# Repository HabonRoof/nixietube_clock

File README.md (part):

# Nixie Clock Firmware

Open-source ESP-IDF firmware for a multiplexed Nixie clock powered by an ESP32-S3. Hardware display boards include IN-4 and IN-18 variants; at boot the firmware senses `DISPLAY_TYPE` (GPIO 19) and selects an IN-4 (6) or IN-14 (6/8) drive profile. RGB backlighting, audio playback, battery management, and a built-in web configuration UI are included.

Whether you want to hack on display effects, add CLI tools, improve the web UI, or bring up new hardware, this guide will get you building with [PlatformIO](https://platformio.org/) quickly.

## Features

- **Nixie display** — Multiplexed control via PCA9685 PWM drivers and a 74HC238 anode mux (tube count and chip count follow the detected display-board profile).
- **RGB backlight** — WS2812 addressable LEDs (4 per tube) with static, breath, rainbow, and off effects.
- **Audio** — DFPlayer Mini integration for sound effects and announcements.
- **RTC** — DS3231 for precise timekeeping with periodic resync to ESP32 system time.
- **Web UI** — On-demand config Wi-Fi AP (`NixieClock-XXXX` / `nixie2026`) with HTTP settings; long-press **button 1 + button 2** (3 s) to enter config mode.
- **NTP sync** — Optional home WiFi credentials; daily ~06:00 local brief STA session writes NTP to DS3231 and verifies RTC error < 1 min (retries on failure).
- **Buttons** — Debounced physical inputs for display mode, backlight profile, and interactive modes.
- **Hibernate mode** — Scheduled daily window turns off tubes and LED backlight. Press any button for a 5-second clock preview (tubes at fixed brightness 50, LED off).
- **Idle standby** — After 1 minute without button presses in clock mode, dim nixie and backlight brightness to 25% of the active profile; any button press restores full brightness.
- **Auto cathode anti-poisoning** — Every 15 minutes, run the same cathode-poisoning digit sweep as manual mode, then auto-return to the clock.
- **Serial CLI** — Interactive console for development, diagnostics, and power-rail control.
- **Power management** — BQ25601 battery charger, BQ27441 fuel gauge, and switched HV / DFPlayer rails.
- **Persistent settings** — Clock preferences stored in NVS and restored on boot.
- **Modular architecture** — FreeRTOS daemons coordinated by a central system controller.

## Developing with PlatformIO

This project uses **PlatformIO + ESP-IDF**. You can work from VS Code / Cursor or from the CLI.

### 1. Install tools

1. Install [Git](https://git-scm.com/) and [Python 3](https://www.python.org/downloads/) (needed for the git-version build script).
2. Install either:
   - **Recommended:** [VS Code](https://code.visualstudio.com/) or Cursor with the [PlatformIO IDE](https://platformio.org/install/ide?install=vscode) extension, or
   - [PlatformIO Core (CLI)](https://docs.platformio.org/en/latest/core/installation.html) alone.
   For now, the PlatformIO for cursor is not stable, so I recommand to use VSCode to compile and use Cursor for coding. 

Opening this repo in VS Code / Cursor should prompt you to install the recommended `platformio.platformio-ide` extension (see `.vscode/extensions.json`).

### 2. Clone and open the project

```bash
git clone https://github.com/HabonRoof/nixietube_clock.git
cd nixietube_clock
```

In VS Code / Cursor: **File → Open Folder** and select the repo root (the folder that contains `platformio.ini`).

First build will download the Espressif platform, ESP-IDF toolchain, and dependencies into `.pio/` — expect a few minutes on a clean machine.

### 3. Pick a build environment

Defined in `platformio.ini`:

| Environment | Board | Use case |
| :--- | :--- | :--- |
| `esp32_s3_devkitc_1` | ESP32-S3-DevKitC-1 | General development / bring-up |
| `esp32_s3_nixie` (default) | Custom `esp32-s3-nixie` (`boards/`) | Production Nixie clock board |

Switch the active env in the PlatformIO status bar, or pass `-e <name>` on the CLI.

### 4. Everyday commands

| Action | CLI | VS Code / Cursor (PlatformIO) |
| :--- | :--- | :--- |
| Build | `pio run` | Build (✓) |
| Flash | `pio run -t upload` | Upload (→) |
| Serial monitor | `pio run -t monitor` | Serial Monitor (🔌) |
| Build + flash + monitor | `pio run -t upload && pio run -t monitor` | Upload and Monitor |
| Clean | `pio run -t clean` | Clean |
| Build for Nixie board | `pio run -e esp32_s3_nixie` | Select `esp32_s3_nixie` env, then Build |

Serial monitor is **115200 baud** (8N1). After connect you should see boot logs and the CLI prompt `nixie_clock> `.

Useful PlatformIO tips:

```bash
# Rebuild from a clean slate
pio run -t clean && pio run

# Flash a specific env, then open the monitor
pio run -e esp32_s3_devkitc_1 -t upload
pio run -t monitor

# List detected serial ports if upload fails
pio device list
```

The build embeds the current git commit hash via `generate_git_version.py` (`get_fw_version` in the CLI).

### 5. Verify you are up and running

1. Flash firmware and open the serial monitor.
2. Type `help` at `nixie_clock> ` to list CLI commands.
3. **Long-press button 1 + button 2** (3 s together) to open the config Wi-Fi AP. Nixie tubes show a 4-digit session code; join `NixieClock-XXXX` (password `nixie2026`) and open `http://192.168.8.8/`.

If something fails to compile or upload, check:

- Use USB Type-A to Type-C cable, the hardware is not support to connect C to C cable for uploading.
- The board is in download mode / USB cable is data-capable.
- The correct env is selected (`esp32_s3_devkitc_1` vs `esp32_s3_nixie`).
- Python can run `generate_git_version.py` from the project root.
- Antivirus or missing udev/driver issues are not blocking the serial port (Windows often needs the CP2102 USB serial driver).

### 6. Where to start hacking

| Goal | Start here |
| :--- | :--- |
| Boot / wiring of subsystems | `src/main.cpp` |
| Mode logic, time, settings | `src/system_controller.*` |
| Tubes / LED effects | `src/daemons/display_daemon.*` |
| Buttons | `src/daemons/input_daemon.*` |
| Audio / DFPlayer | `src/daemons/audio_daemon.*` |
| Serial commands | `src/daemons/cli_daemon.*` |
| Web settings UI | `src/web_server.cpp`, `src/web_page.cpp` |
| Device drivers | `lib/drivers/`, `lib/include/` |
| Shared messages / state | `lib/include/message_types.h`, `src/system_state.*` |

## Software Structure

The firmware is split into clear layers so new contributors can find the right file quickly.

```text
┌─────────────────────────────────────────────────────────────┐
│  Interfaces                                                 │
│    WebServer  ·  CliDaemon  ·  InputDaemon (buttons)        │
├─────────────────────────────────────────────────────────────┤
│  Coordination                                               │
│    SystemController  ·  SystemState (NVS)                   │
├─────────────────────────────────────────────────────────────┤
│  FreeRTOS daemons                                           │
│    DisplayDaemon  ·  AudioDaemon                            │
├─────────────────────────────────────────────────────────────┤
│  App drivers / services                                     │
│    NixieDriver · LedDriver · AudioDriver                    │
│    PowerController · ChargerController · GasgaugeService    │
├─────────────────────────────────────────────────────────────┤
│  Hardware drivers (lib/drivers)                             │
│    PCA9685 · WS2812 · DFPlayer · DS3231 · BQ25601 · BQ27441 │
└─────────────────────────────────────────────────────────────┘
```

### Directory map

```text
nixietube_clock/
├── platformio.ini          # PlatformIO envs, ESP-IDF, build flags
├── boards/                 # Custom board JSON (esp32-s3-nixie)
├── generate_git_version.py # Embeds git hash into the firmware
│
├── src/                    # Application code (what most PRs touch)
│   ├── main.cpp            # Boot: NVS, drivers, start daemons
│   ├── system_controller.* # Central coordinator (time, modes, settings)
│   ├── system_state.*      # Thread-safe settings / battery / time + NVS
│   ├── web_server.*        # Wi-Fi AP + HTTP API
│   ├── web_page.*          # Embedded settings HTML/JS
│   ├── settings_json.*     # ClockSettings ↔ nested JSON
│   ├── web_json.*          # HTTP JSON body / response helpers
│   ├── nixie_driver.*      # High-level tube multiplexing
│   ├── led_driver.*        # High-level WS2812 control
│   ├── audio_driver.*      # High-level DFPlayer wrapper
│   ├── power_controller.*  # HV / DFPlayer rail switching
│   ├── charger_controller.*
│   ├── gasgauge_service.*
│   ├── color_model.cpp     # Color helpers for backlight
│   └── daemons/
│       ├── display_daemon.*  # Nixie + LED effects @ 50 Hz
│       ├── audio_daemon.*    # Async audio commands
│       ├── input_daemon.*    # Button debounce → SystemController
│       └── cli_daemon.*      # Serial console
│
├── lib/
│   ├── include/            # Public headers / interfaces / message types
│   └── drivers/            # Low-level IC drivers (I2C/UART/RMT/GPIO)
│       ├── pca9685/
│       ├── ws2812/
│       ├── dfplayer/
│       ├── ds3231/
│       ├── bq25601/
│       ├── bq27441/
│       ├── i2c_bus/
│       ├── power_switch/
│       └── display_board/
│
├── hardware/               # KiCad schematics & PCBs (main, display, HV)
├── test/                   # Manual CLI tests and component experiments
└── doc/                    # Datasheets, photos, architecture drawings
    ├── web_api.md          # HTTP JSON API schemas
    ├── state_machine.drawio  # Behavioral modes (six pages, kept in sync with firmware)
    └── structure.drawio    # Early aspirational block diagram (outdated)
```

### Responsibility cheat sheet

| Module | Role |
| :--- | :--- |
| `main.cpp` | Creates drivers/services, wires dependencies, starts tasks |
| `SystemController` | Owns RTC sync, display mode / backlight / alarm logic; single writer for settings |
| `SystemState` | Shared snapshots + NVS load/save |
| `DisplayDaemon` | Tube digits, LED effects, 50 Hz update loop |
| `AudioDaemon` | Plays/pauses tracks; powers DFPlayer rail via `PowerController` |
| `InputDaemon` | Polls/debounces BTN_0–2 and posts presses to `SystemController` |
| `CliDaemon` / `WebServer` | External control surfaces; request settings through `SystemController` |
| `lib/drivers/*` | Talk to chips; keep bus/register details out of app logic |

Cross-task communication uses FreeRTOS queues and types in `lib/include/message_types.h`. Prefer posting messages (or `SystemController::request_settings_update()`) over reaching into another daemon’s private state.

## Hardware Configuration

Pin assignments are defined in `src/system_controller.cpp` and `lib/drivers/power_switch/gpio_power_switch.h`.

| Peripheral | Pin Name | GPIO | Description |
| :--- | :--- | :--- | :--- |
| **I2C0** | SDA | GPIO 6 | PCA9685 (display), BQ25601, BQ27441 |
| | SCL | GPIO 5 | I2C0 clock (400 kHz) |
| **I2C1** | SDA | GPIO 18 | DS3231 RTC, LTR-303 (display) |
| | SCL | GPIO 17 | I2C1 clock (400 kHz) |
| **UART** | TX | GPIO 42 | Audio TX → DFPlayer RX |
| | RX | GPIO 41 | Audio RX ← DFPlayer TX |
| **GPIO** | RTC_INT | GPIO 2 | DS3231 interrupt (active low) |
| | BTN_0 | GPIO 8 | Alarm stop / pomodoro start / divergence re-trigger |
| | BTN_1 | GPIO 12 | Display mode cycle |
| | BTN_2 | GPIO 13 | Backlight profile cycle |
| | PCA_OE | GPIO 4 | PCA9685 output enable (active low) |
| | ANODE_A0–A2 | GPIO 9–11 | 74HC238 anode mux address lines |
| | DISPLAY_TYPE | GPIO 19 | Analog strap for display-board type (ADC2 CH8) |
| | HV_PWR | GPIO 15 | HV power rail enable (via `GpioPowerSwitch`) |
| | DF_PWR | GPIO 16 | DFPlayer power rail enable (via `GpioPowerSwitch`) |
| **RMT** | LED_DATA | GPIO 7 | WS2812 LED data line |

`DISPLAY_TYPE` strap voltages map to firmware profiles: ~0 V → IN-4 (6 tubes, 4× PCA9685); ~1.65 V → IN-14 (8 tubes, 5× PCA9685); ~3.3 V → IN-14 (6 tubes, 4× PCA9685). KiCad projects under `hardware/` include `display_board_in4` and `display_board_in18` (IN-18 boards use the matching strap / profile configured on the PCB).

## Architecture

The firmware runs on FreeRTOS and uses a daemon-based design. `SystemState` holds shared, thread-safe snapshots of settings, battery, and time status.

```mermaid
flowchart TB
    subgraph Interfaces
        Web[WebServer]
        CLI[CliDaemon]
        IN[InputDaemon]
    end

    SC[SystemController]
    DD[DisplayDaemon]
    AD[AudioDaemon]
    CC[ChargerController]
    PC[PowerController]

    Web --> SC
    CLI --> SC
    CLI --> CC
    CLI --> PC
    CLI --> AD
    IN --> SC

    SC --> DD
    SC --> AD
    SC --> SystemState[(SystemState / NVS)]

    DD --> Nixie[NixieDriver / PCA9685]
    DD --> LED[LedDriver / WS2812]
    AD --> Audio[AudioDriver / DFPlayer]
    AD --> PC
    SC --> RTC[DS3231]
    SC --> GG[GasgaugeService / BQ27441]
    CC --> Charger[BQ25601]
    PC --> Rails[HV & DFPlayer rails]
```

### System Controller (`src/system_controller.cpp`)

Central coordinator that:

- Initializes I2C, UART, RMT, and GPIO peripherals.
- Owns the DS3231 RTC and maintains ESP32 system time (UTC).
- Periodically resyncs from the RTC and publishes time status.
- Polls the BQ27441 fuel gauge and updates battery status.
- Dispatches 1 Hz time updates to `DisplayDaemon`.
- Handles button presses from `InputDaemon` (modes, backlight, pomodoro / alarm).
- Accepts thread-safe settings changes from the web UI and CLI.

### Display Daemon (`src/daemons/display_daemon.cpp`)

Manages all visual output:

- Drives Nixie tubes via `NixieDriver` (dedicated high-priority multiplexing task).
- Drives LED backlights via `LedDriver`.
- Runs the LED effects engine (static, breath, rainbow, off).
- Updates hardware at 50 Hz.

#### Display modes (BTN_1 cycle)

Press **BTN_1** to cycle through display modes in this order:

1. **Clock** (`HHMMSS`) — normal time display
2. **Date** (`YYMMDD`) — current date
3. **Pomodoro** — 25-minute work / 5-minute break timer
4. **Divergence meter** — random digit animation (auto-returns to clock)
5. **Cathode poisoning** — digit sweep on all tubes (auto-returns to clock)

**Pomodoro mode:** On entry the display shows `002500` with a static red backlight (brightness follows your profile). Press **BTN_0** to start the countdown; the backlight breathes red during work and green during break. Work and break sessions alternate automatically until you cycle away with **BTN_1**, which restores your backlight profile.

### Input Daemon (`src/daemons/input_daemon.cpp`)

Polls the three front-panel buttons every 20 ms with debounce / inter-press filtering, then posts press events to `SystemController`. **Button 2** short press cycles backlight profiles; **long press button 1 + button 2** (3 s) opens or closes the config Wi-Fi AP. Pin map: `lib/include/button_config.h`.

### Audio Daemon (`src/daemons/audio_daemon.cpp`)

Handles asynchronous audio commands (play, stop, volume) and communicates with the DFPlayer Mini. Uses `PowerController` to switch the DFPlayer power rail.

### Web Server (`src/web_server.cpp`, `src/web_page.cpp`)

On-demand config Wi-Fi AP and embedded HTTP server (active only in config mode):

| Setting | Value |
| :--- | :--- |
| Enter config | Long-press button 1 + button 2 for 3 s (same combo exits when AP is active) |
| SSID | `NixieClock-XXXX` (random 4-digit code each session; shown on Nixie tubes) |
| Password | `nixie2026` |
| AP IP | `192.168.8.8` |
| Timeout | 15 min max, or 2 min after all clients disconnect |

Connect to the AP and open `http://192.168.8.8/`. Use **完成並關閉設定 WiFi** when done.

| Endpoint | Method | Description |
| :--- | :--- | :--- |
| `/` | GET | Settings web UI |
| `/api/settings` | GET/POST | Clock settings (JSON); see [doc/web_api.md](doc/web_api.md) |
| `/api/ap/status` | GET | Config AP SSID, session code, remaining time |
| `/api/ap/stop` | POST | Stop config AP (deauth + shutdown) |
| `/api/wifi` | GET/POST/DELETE | Home WiFi for daily NTP sync |
| `/api/ntp/status` | GET | Last NTP sync status |
| `/api/time` | GET | Local time, RTC status, temperature |
| `/api/audio/*` | GET/POST | MP3 tracks and playback |

Home WiFi credentials enable a brief daily STA session at **06:00 local** for NTP → DS3231 sync (always write, verify RTC within 1 min, retry up to 3×); WiFi is off the rest of the time.

Full schemas: [doc/web_api.md](doc/web_api.md). Without hardware, `python3 scripts/mock_web_ui.py` serves this same page at `http://127.0.0.1:8080/` with in-memory stand-ins for the JSON API. See [scripts/README.md](scripts/README.md).

Configurable settings include timezone offset, alarm, backlight, nixie brightness/transition, volume, profiles, hibernation, and home WiFi. The web **Light** tab provides live display preview; **Save 1–4** commits a profile. Short-press button 2 to switch profiles on the device.

### CLI Daemon (`src/daemons/cli_daemon.cpp`)

Interactive serial console for development, diagnostics, and factory setup. Connect at **115200 baud** (8N1, no flow control) via USB or UART. The prompt is `nixie_clock> `. Type `help` for a summary of all commands.

```bash
pio run -t monitor
```

#### Display and backlight

| Command | Description |
| :--- | :--- |
| `set_nixie --number <n>` | Display a 6-digit number on the tubes |
| `set_backlight --rgb R,G,B --brightness N` | Set backlight color and brightness (0–255) |

#### Device info

| Command | Description |
| :--- | :--- |
| `get_uuid` | Wi-Fi MAC-based device ID |
| `get_hw_version` | ESP32-S3 chip and board revision |
| `get_fw_version` | Git commit hash and ESP-IDF version |
| `reboot` | Restart the device |

#### RTC and alarm (`rtctool`)

The DS3231 RTC stores **UTC** internally; CLI time and alarm values are **local wall clock** and are converted using the configured timezone offset. Set operations are asynchronous — run `rtctool read` afterward to confirm.

| Subcommand | Description |
| :--- | :--- |
| `rtctool read` | Read local time, UTC epoch, timezone, calibration/OSF status, temperature, and alarm settings |
| `rtctool set_tz <offset_hours>` | Set timezone offset (-12..+14) |
| `rtctool set_time <YYYY-MM-DD HH:MM:SS>` | Calibrate RTC and system clock (marks RTC as calibrated) |
| `rtctool set_alarm <HH:MM:SS> [--enable\|--disable] [--track <n>]` | Set daily alarm time; enables alarm by default |

Example workflow:

```text
nixie_clock> rtctool set_tz 8
nixie_clock> rtctool set_time 2026-07-06 16:30:00
nixie_clock> rtctool set_alarm 07:30:00 --enable --track 1
nixie_clock> rtctool read
```

To disable the alarm without changing its time:

```text
nixie_clock> rtctool set_alarm 07:30:00 --disable
```

#### Power and charging

| Command | Description |
| :--- | :--- |
| `get_bq25601_status` | Read BQ25601 charger status registers |
| `enable_charging` / `disable_charging` | Control battery charging |
| `enable_hv` / `disable_hv` | Control HV power rail |
| `enable_df_power` / `disable_df_power` | Control DFPlayer power rail |

#### DFPlayer audio (`dftool`)

Commands talk to the `AudioDaemon`, which powers the DFPlayer rail automatically when needed. Place MP3 files in an `mp3` folder on the SD card root and name them `0001.mp3`, `0002.mp3`, etc. (up to 9999). Track numbers match the numeric prefix in each filename.

| Subcommand | Description |
| :--- | :--- |
| `dftool list` | List tracks in the SD card `mp3/` folder |
| `dftool status` | Show current track, playback state, and track count |
| `dftool play <track> [--loop]` | Play a track; add `--loop` for repeat |
| `dftool toggle <track>` | Play/pause toggle (same behavior as the web UI) |
| `dftool pause` | Pause playback |
| `dftool resume` | Resume playback |
| `dftool stop` | Stop playback |
| `dftool next` | Play next track |
| `dftool prev` | Play previous track |
| `dftool volume <0-30>` | Set volume (DFPlayer range) |
| `dftool vol_up` / `dftool vol_down` | Step volume up or down |

Example workflow:

```text
nixie_clock> dftool list
nixie_clock> dftool play 1
nixie_clock> dftool status
nixie_clock> dftool pause
nixie_clock> dftool resume
nixie_clock> dftool volume 20
nixie_clock> dftool stop
```

#### Fuel gauge (`ggtool`)

| Subcommand | Description |
| :--- | :--- |
| `ggtool status` | Probe BQ27441 device info and gauging readiness |
| `ggtool read` | Read live SOC, SOH, voltage, and current |
| `ggtool cache` | Read last cached battery values from `SystemState` |
| `ggtool peek <reg_hex> [len]` | Dump raw register bytes |
| `ggtool block [class] [index]` | Dump a 32-byte state block |
| `ggtool config [mAh]` | Configure design capacity |

See `test/test_cli/README.md` for a manual test plan and automated test script.

### Drivers (`lib/drivers/`, `src/*_driver.cpp`)

| Driver | Role |
| :--- | :--- |
| `NixieDriver` | PCA9685 multiplexing; chip/tube count from `display_board_config` profile |
| `LedDriver` | RMT-based WS2812 control |
| `AudioDriver` | High-level DFPlayer Mini interface |
| `Ds3231` | RTC read/write and temperature |
| `Bq25601` | Battery charger IC |
| `Bq27441` | Fuel gauge IC |
| `GpioPowerSwitch` | HV and DFPlayer power-rail switching |

## Development Guide

### Adding a New LED Effect

1. Add a method such as `run_my_effect(uint32_t dt_ms)` in `DisplayDaemon`.
   Use `apply_backlight_to_all(state)` or manipulate `led_driver_` directly.
2. Add an entry to the `LedEffectType` enum in `display_daemon.h`.
3. Update `DisplayDaemon::process_message` to handle the new effect type.
4. Update `DisplayDaemon::update_effects` to call the new method.
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
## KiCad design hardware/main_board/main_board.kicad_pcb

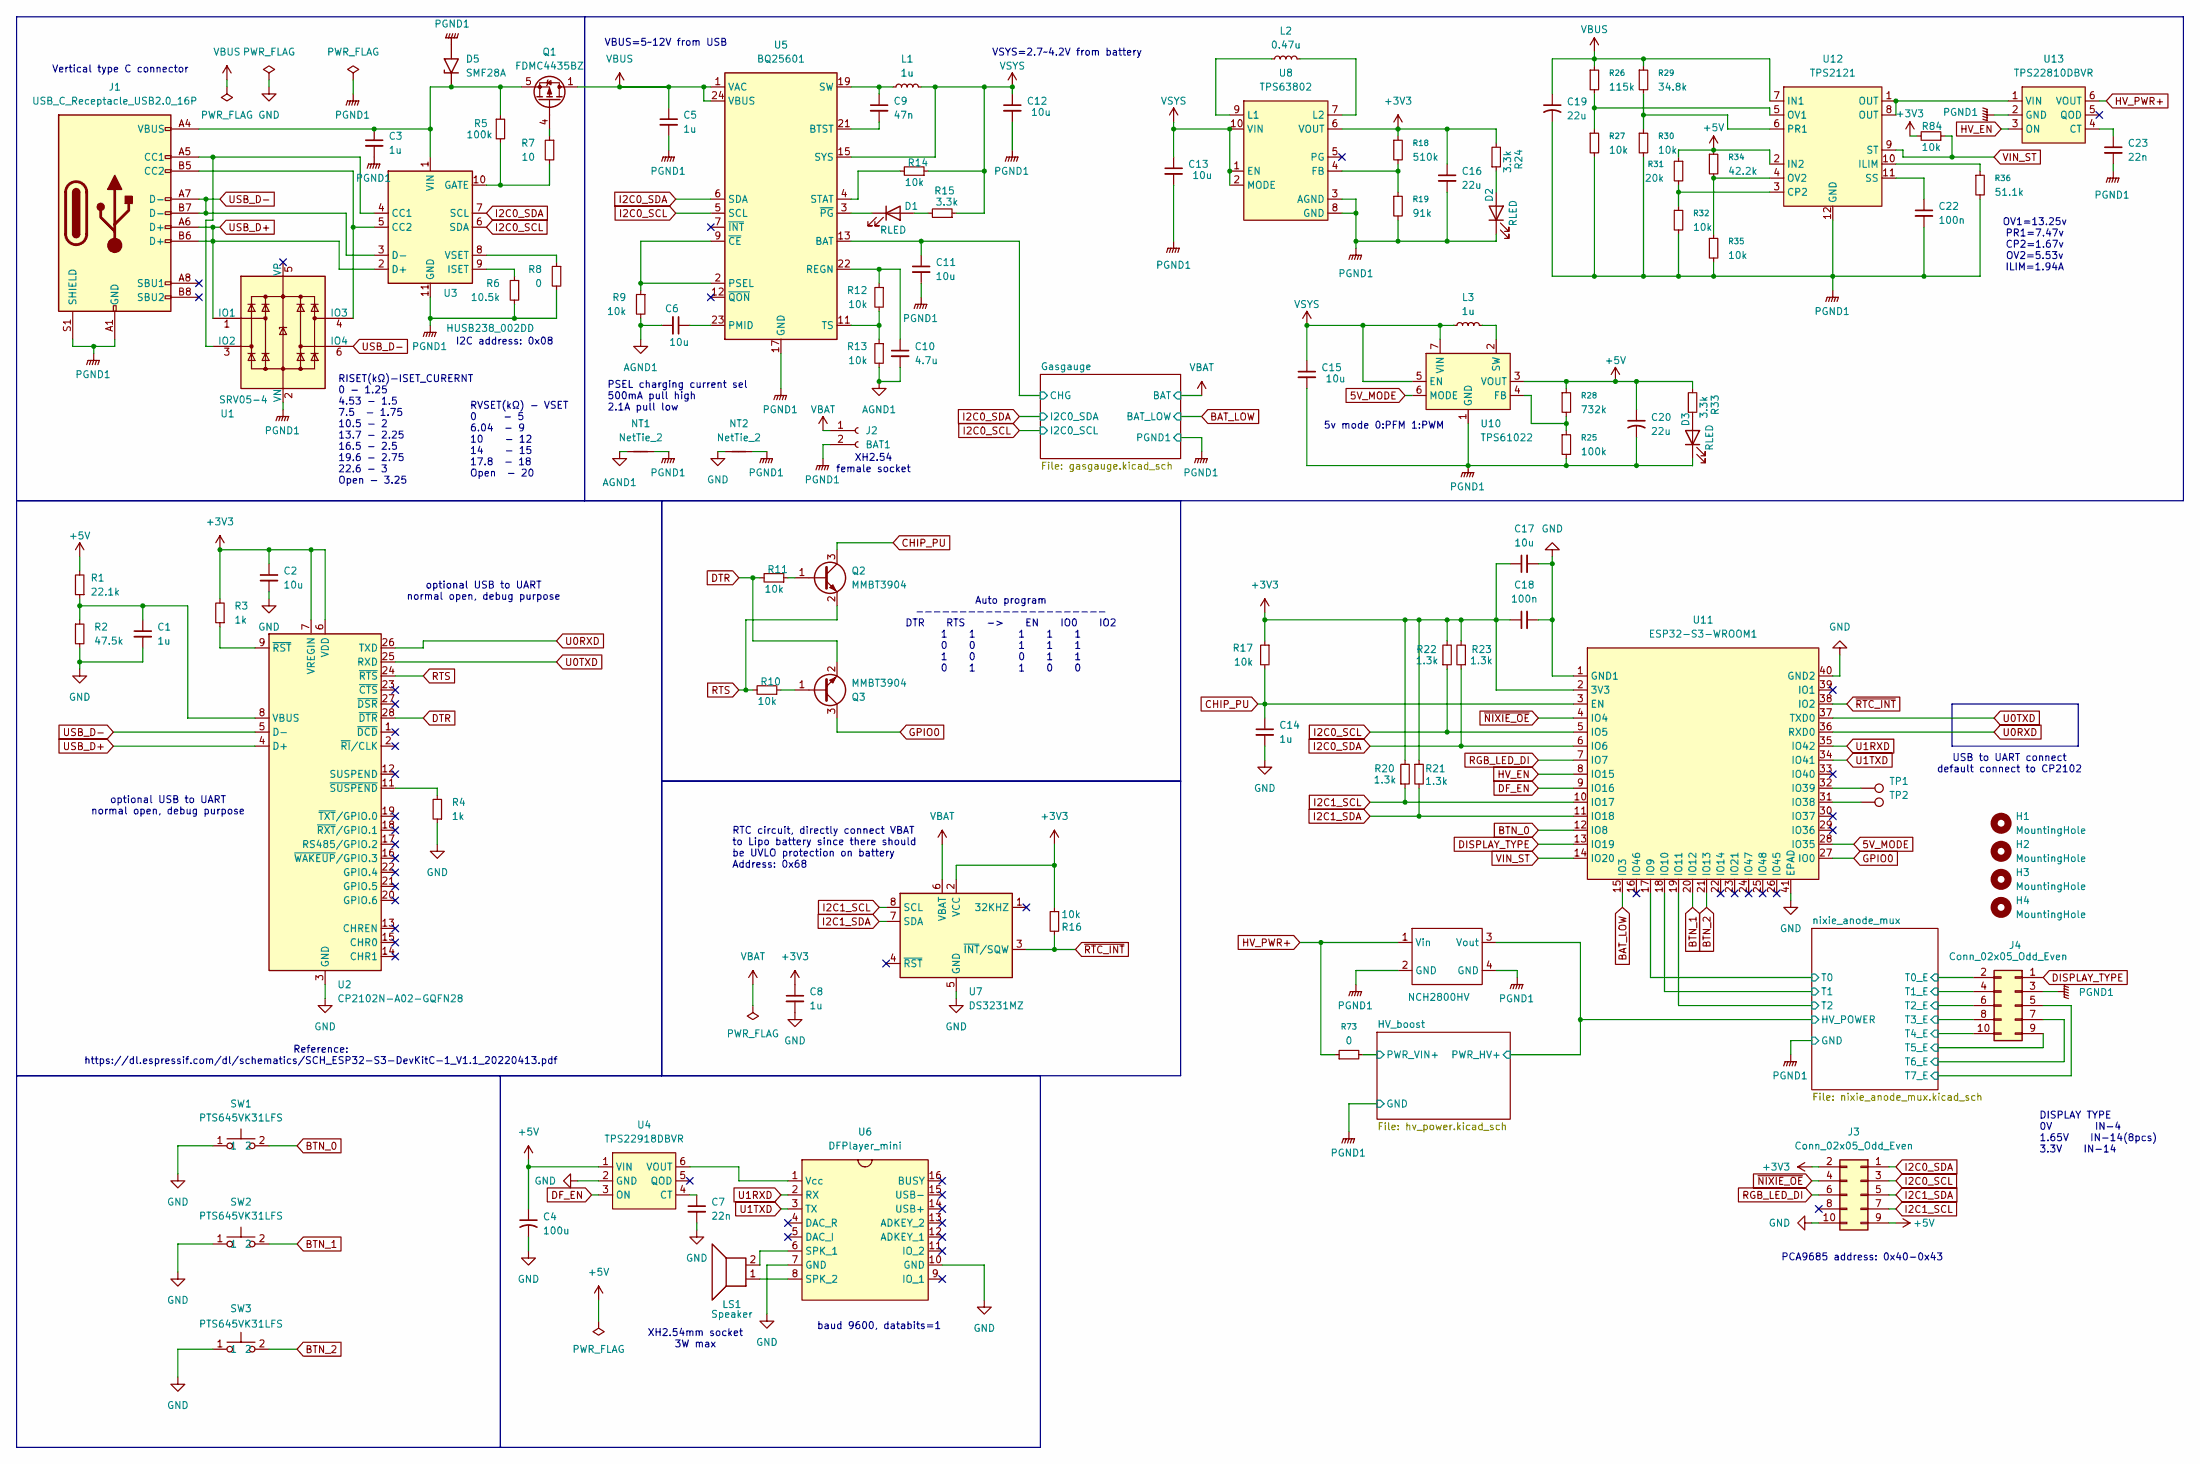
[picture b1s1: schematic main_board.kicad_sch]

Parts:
C1, C3, C5, C8, C14: 1u; C_0603_1608Metric; LCSC PN C5199872
C2, C6, C11, C17: 10u; C_0603_1608Metric; LCSC PN C19702
C4: 100u; C_Elec_6.3x5.4; LCSC PN C2887276
C7: 22n; C_0603_1608Metric; LCSC PN C106222
C9: 47n; C_0603_1608Metric; LCSC PN C1622
C10: 4.7u; C_0603_1608Metric; LCSC PN C18185770
C12: 10u; C_0805_2012Metric; LCSC PN C6119932
C13, C15: 10u; CP_EIA-2012-12_Kemet-R; LCSC PN C129234
C16: 22u; C_0805_2012Metric; LCSC PN C23692981
C18, C22: 100n; C_0402_1005Metric; LCSC PN C1525
C19, C20: 22u; C_Elec_5x5.4; LCSC PN C970662
C23: 22n; C_0402_1005Metric; LCSC PN C1532
D1, D2, D3: RLED; LED_0603_1608Metric; LCSC PN C2286
D5: SMF28A; D_SMF
H1, H2, H3, H4: MountingHole; MountingHole_3.2mm_M3_DIN965
J1: USB_C_Receptacle_USB2.0_16P; USB_C_Receptacle_G-Switch_GT-USB-7051x; LCSC PN C2843970
J2: BAT1; JST_PH_S2B-PH-SM4-TB_1x02-1MP_P2.00mm_Horizontal; LCSC PN C3029440
J3, J4: Conn_02x05_Odd_Even; PinHeader_2x05_P2.00mm_Vertical; LCSC PN C42385473
L1: 1u; L_Wuerth_PMCI-252010; LCSC PN C696436
L2: 0.47u; Murata_201612E; LCSC PN C668312
L3: 1u; L_Coilcraft_XAL6030-XXX; LCSC PN C5157561
LS1: Speaker; JST_PH_S2B-PH-SM4-TB_1x02-1MP_P2.00mm_Horizontal; LCSC PN C3029440
NT1, NT2: NetTie_2; NetTie-2_SMD_Pad0.5mm
Q1: FDMC4435BZ; VSON-8_3.3x3.3mm_P0.65mm_NexFET; LCSC PN C556450
Q2, Q3: MMBT3904; SOT-23; LCSC PN C81464
R1: 22.1k; R_0402_1005Metric; LCSC PN C43473
R2: 47.5k; R_0402_1005Metric; LCSC PN C103064
R3, R4: 1k; R_0402_1005Metric; LCSC PN C11702
R5, R25: 100k; R_0402_1005Metric; LCSC PN C25741
R6: 10.5k; R_0402_1005Metric; LCSC PN C25850
R7: 10; R_0402_1005Metric; LCSC PN C25077
R8: 0; R_0402_1005Metric; LCSC PN C17168
R9, R10, R11, R12, R13, R14, R16, R17, R84: 10k; R_0402_1005Metric; LCSC PN C25744
R15, R24, R33: 3.3k; R_0402_1005Metric; LCSC PN C25890
R18: 510k; R_0402_1005Metric; LCSC PN C100463
R19: 91k; R_0402_1005Metric; LCSC PN C284722
R20, R21: 1.3k; R_0402_1005Metric; LCSC PN C25900
R22, R23: 1.3k; R_0402_1005Metric; LCSC PN C881388
R26: 115k; R_0603_1608Metric; LCSC PN C227555
R27, R30, R32, R35: 10k; R_0603_1608Metric; LCSC PN C98220
R28: 732k; R_0402_1005Metric; LCSC PN C27016
R29: 34.8k; R_0603_1608Metric; LCSC PN C23141
R31: 20k; R_0603_1608Metric; LCSC PN C4184
R34: 42.2k; R_0603_1608Metric; LCSC PN C227896
R36: 51.1k; C_0603_1608Metric; LCSC PN C23072
R73: 0; R_0603_1608Metric; LCSC PN C21189
SW1, SW2, SW3: PTS645VK31LFS; LCSC PN C2804591
TP1, TP2: TestPoint; TestPoint_Pad_1.5x1.5mm
U1: SRV05-4; SOT-23-6; LCSC PN C13612
U2: CP2102N-A02-GQFN28; QFN-28-1EP_5x5mm_P0.5mm_EP3.35x3.35mm; LCSC PN C964632
U3: HUSB238_002DD; WDFN-10-1EP_3x3mm_P0.5mm_EP1.8x2.5mm; LCSC PN C7471904
U4: TPS22918DBVR; SOT-23-6; LCSC PN C131941
U5: BQ25601; Texas_RTW_WQFN-24-1EP_4x4mm_P0.5mm_EP2.7x2.7mm_ThermalVias; LCSC PN C468236
U6: DFPlayer_mini
U7: DS3231MZ; SOIC-8_3.9x4.9mm_P1.27mm; LCSC PN C107410
U8: TPS63802; VSON-10-HR-DLA; LCSC PN C2845237
U9: NCH2800HV; NCH8200HV
U10: TPS61022; Texas_RWU0007A_VQFN-7_2x2mm_P0.5mm; LCSC PN C2071784
U11: ESP32-S3-WROOM1; ESP32-S3-WROOM-1; LCSC PN C2913198
U12: TPS2121; Texas_VQFN-HR-12_2x2.5mm_P0.5mm_ThermalVias; LCSC PN C2156025
U13: TPS22810DBVR; SOT-23-6; LCSC PN C205990

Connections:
5V_MODE: U10.6 (MODE), U11.28 (IO35)
+3V3: C2.1, C8.1, C16.1, C17.1, C18.1, J3.2, R3.2, R16.1, R17.1, R18.1, R20.2, R21.1, R22.2, R23.2, R24.2, R84.2, U2.6 (VDD), U2.7 (VREGIN), U7.2 (VCC), U8.6 (VOUT), U11.2 (3V3); also elsewhere on the board
+5V: C4.1, C20.1, J3.9, R1.2, R28.1, R31.1, R33.2, R34.1, U4.1 (VIN), U10.3 (VOUT), U12.2 (IN2)
/Gasgauge/CHG: C11.1, U5.13 (BAT), U5.14 (BAT); also elsewhere on the board
/HV_boost/PWR_HV+: U9.3 (Vout); also elsewhere on the board
/HV_boost/PWR_VIN+: R73.2; also elsewhere on the board
/nixie_anode_mux/T0: U11.17 (IO9); also elsewhere on the board
/nixie_anode_mux/T0_E: J4.2; also elsewhere on the board
/nixie_anode_mux/T1: U11.18 (IO10); also elsewhere on the board
/nixie_anode_mux/T1_E: J4.4; also elsewhere on the board
/nixie_anode_mux/T2: U11.19 (IO11); also elsewhere on the board
/nixie_anode_mux/T2_E: J4.6; also elsewhere on the board
/nixie_anode_mux/T3_E: J4.8; also elsewhere on the board
/nixie_anode_mux/T4_E: J4.10; also elsewhere on the board
/nixie_anode_mux/T5_E: J4.9; also elsewhere on the board
/nixie_anode_mux/T6_E: J4.7; also elsewhere on the board
/nixie_anode_mux/T7_E: J4.5; also elsewhere on the board
AGND1: C6.2, C10.2, NT1.1, R9.2, R13.2
BAT_LOW: U11.15 (IO3); also elsewhere on the board
BTN_0: SW1.2, U11.12 (IO8)
BTN_1: SW2.2, U11.20 (IO12)
BTN_2: SW3.2, U11.21 (IO13)
CHIP_PU: C14.1, Q2.3 (C), R17.2, U11.3 (EN)
DF_EN: U4.3 (ON), U11.9 (IO16)
DISPLAY_TYPE: J4.1, U11.13 (IO19)
DTR: Q3.2 (E), R11.2, U2.28 (~DTR)
GND: C1.2, C2.2, C4.2, C7.2, C8.2, C14.2, C17.2, C18.2, J3.10, NT2.1, R2.2, R4.1, SW1.1, SW2.1, SW3.1, U2.3 (GND), U2.29 (GND), U4.2 (GND), U6.7 (GND), U6.10 (GND), U7.5 (GND), U11.1 (GND1), U11.40 (GND2), U11.41 (EPAD)
GPIO0: Q3.3 (C), U11.27 (IO0)
HV_EN: U11.8 (IO15), U13.3 (ON)
HV_PWR+: R73.1, U9.1 (Vin), U13.6 (VOUT)
I2C0_SCL: J3.3, R22.1, U3.6 (SDA), U5.5 (SCL), U11.5 (IO5); also elsewhere on the board
I2C0_SDA: J3.1, R23.1, U3.7 (SCL), U5.6 (SDA), U11.6 (IO6); also elsewhere on the board
I2C1_SCL: J3.7, R20.1, U7.8 (SCL), U11.10 (IO17)
I2C1_SDA: J3.5, R21.2, U7.7 (SDA), U11.11 (IO18)
unnamed: C9.1, L1.1, U5.19 (SW), U5.20 (SW)
unnamed: D1.2 (A), R15.2
unnamed: D1.1 (K), U5.3 (~PG)
unnamed: D2.2 (A), R24.1
unnamed: D3.2 (A), R33.1
unnamed: C3.1, D5.1 (A1), J1.A4 (VBUS), J1.A9 (VBUS), J1.B4 (VBUS), J1.B9 (VBUS), Q1.5 (D), R5.1, U3.1 (VIN)
unnamed: J1.A5 (CC1), U1.3 (IO2), U3.4 (CC1)
unnamed: J1.B5 (CC2), U1.4 (IO3), U3.5 (CC2)
unnamed: Q1.4 (G), R7.1
unnamed: Q2.1 (B), R11.1
unnamed: Q3.1 (B), R10.1
unnamed: C1.1, R1.1, R2.1, U2.8 (VBUS)
unnamed: R3.1, U2.9 (~RST)
unnamed: R4.2, U2.11 (~SUSPEND)
unnamed: R5.2, R7.2, U3.10 (GATE)
unnamed: R6.1, U3.9 (ISET)
unnamed: R8.1, U3.8 (VSET)
unnamed: C7.1, U4.4 (CT)
unnamed: U4.6 (VOUT), U6.1 (Vcc)
unnamed: C9.2, U5.21 (BTST)
unnamed: C6.1, U5.23 (PMID)
unnamed: R9.1, U5.2 (PSEL), U5.9 (~CE)
unnamed: C10.1, R12.1, U5.22 (REGN)
unnamed: R14.2, U5.4 (STAT)
unnamed: R12.2, R13.1, U5.11 (TS)
unnamed: LS1.2, U6.6 (SPK_1)
unnamed: LS1.1, U6.8 (SPK_2)
unnamed: R18.2, R19.1, U8.4 (FB)
unnamed: L2.1, U8.9 (L1)
unnamed: L2.2, U8.7 (L2)
unnamed: R25.1, R28.2, U10.4 (FB)
unnamed: L3.2, U10.2 (SW)
unnamed: TP2.1, U11.31 (IO38)
unnamed: TP1.1, U11.32 (IO39)
unnamed: R31.2, R32.1, U12.3 (CP2)
unnamed: R36.1, U12.10 (ILIM)
unnamed: R26.2, R27.1, U12.5 (OV1)
unnamed: R34.2, R35.1, U12.4 (OV2)
unnamed: R29.2, R30.1, U12.6 (PR1)
unnamed: C22.1, U12.11 (SS)
unnamed: C23.1, U13.4 (CT)
unnamed: U12.1 (OUT), U12.8 (OUT), U13.1 (VIN)
PGND1: C3.2, C5.2, C11.2, C12.2, C13.2, C15.2, C16.2, C19.2, C20.2, C22.2, C23.2, D2.1 (K), D3.1 (K), D5.2 (A2), J1.A1 (GND), J1.A12 (GND), J1.B1 (GND), J1.B12 (GND), J1.S1 (SHIELD), J2.2, J4.3, NT1.2, NT2.2, R6.2, R8.2, R19.2, R25.2, R27.2, R30.2, R32.2, R35.2, R36.2, U1.2 (VN), U3.11 (GND), U5.17 (GND), U5.18 (GND), U5.25 (GND), U8.3 (AGND), U8.8 (GND), U9.2 (GND), U9.4 (GND), U10.1 (GND), U12.12 (GND), U13.2 (GND); also elsewhere on the board
RGB_LED_DI: J3.6, U11.7 (IO7)
RTS: Q2.2 (E), R10.2, U2.24 (~RTS)
U0RXD: U2.26 (TXD), U11.36 (RXD0)
U0TXD: U2.25 (RXD), U11.37 (TXD0)
U1RXD: U6.2 (RX), U11.35 (IO42)
U1TXD: U6.3 (TX), U11.34 (IO41)
USB_D+: J1.A6 (D+), J1.B6 (D+), U1.1 (IO1), U2.4 (D+), U3.2 (D+)
USB_D-: J1.A7 (D-), J1.B7 (D-), U1.6 (IO4), U2.5 (D-), U3.3 (D-)
VBAT: J2.1, U7.6 (VBAT); also elsewhere on the board
VBUS: C5.1, C19.1, Q1.1 (S), R26.1, R29.1, U5.1 (VAC), U5.24 (VBUS), U12.7 (IN1)
VIN_ST: R84.1, U11.14 (IO20), U12.9 (ST)
VSYS: C12.1, C13.1, C15.1, L1.2, L3.1, R14.1, R15.1, U5.15 (SYS), U5.16 (SYS), U8.1 (EN), U8.2 (MODE), U8.10 (VIN), U10.5 (EN), U10.7 (VIN)
~NIXIE_OE: J3.4, U11.4 (IO4)
~RTC_INT: R16.2, U7.3 (~INT/SQW), U11.38 (IO2)

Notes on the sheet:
optional USB to UART normal open, debug purpose
PSEL charging current sel 500mA pull high 2.1A pull low
VSYS=2.7~4.2V from battery
I2C address: 0x08
RVSET(kΩ) - VSET 0 - 5 6.04 - 9 10 - 12 14 - 15 17.8 - 18 Open - 20
DISPLAY TYPE 0V IN-4 1.65V IN-14(8pcs) 3.3V IN-14
Auto program ---------------------- DTR RTS -> EN IO0 IO2 1 1 1 1 1 0 0 1 1 1 1 0 0 1 1 0 1 1 0 0
Reference: https://dl.espressif.com/dl/schematics/SCH_ESP32-S3-DevKitC-1_V1.1_20220413.pdf
XH2.54mm socket 3W max
USB to UART connect default connect to CP2102
RISET(kΩ)-ISET_CURERNT 0 - 1.25 4.53 - 1.5 7.5 - 1.75 10.5 - 2 13.7 - 2.25 16.5 - 2.5 19.6 - 2.75 22.6 - 3 Open - 3.25
baud 9600, databits=1
5v mode 0:PFM 1:PWM
Vertical type C connector
XH2.54 female socket
PCA9685 address: 0x40-0x43
OV1=13.25v PR1=7.47v CP2=1.67v OV2=5.53v ILIM=1.94A
RTC circuit, directly connect VBAT to Lipo battery since there should be UVLO protection on battery Address: 0x68
VBUS=5~12V from USB

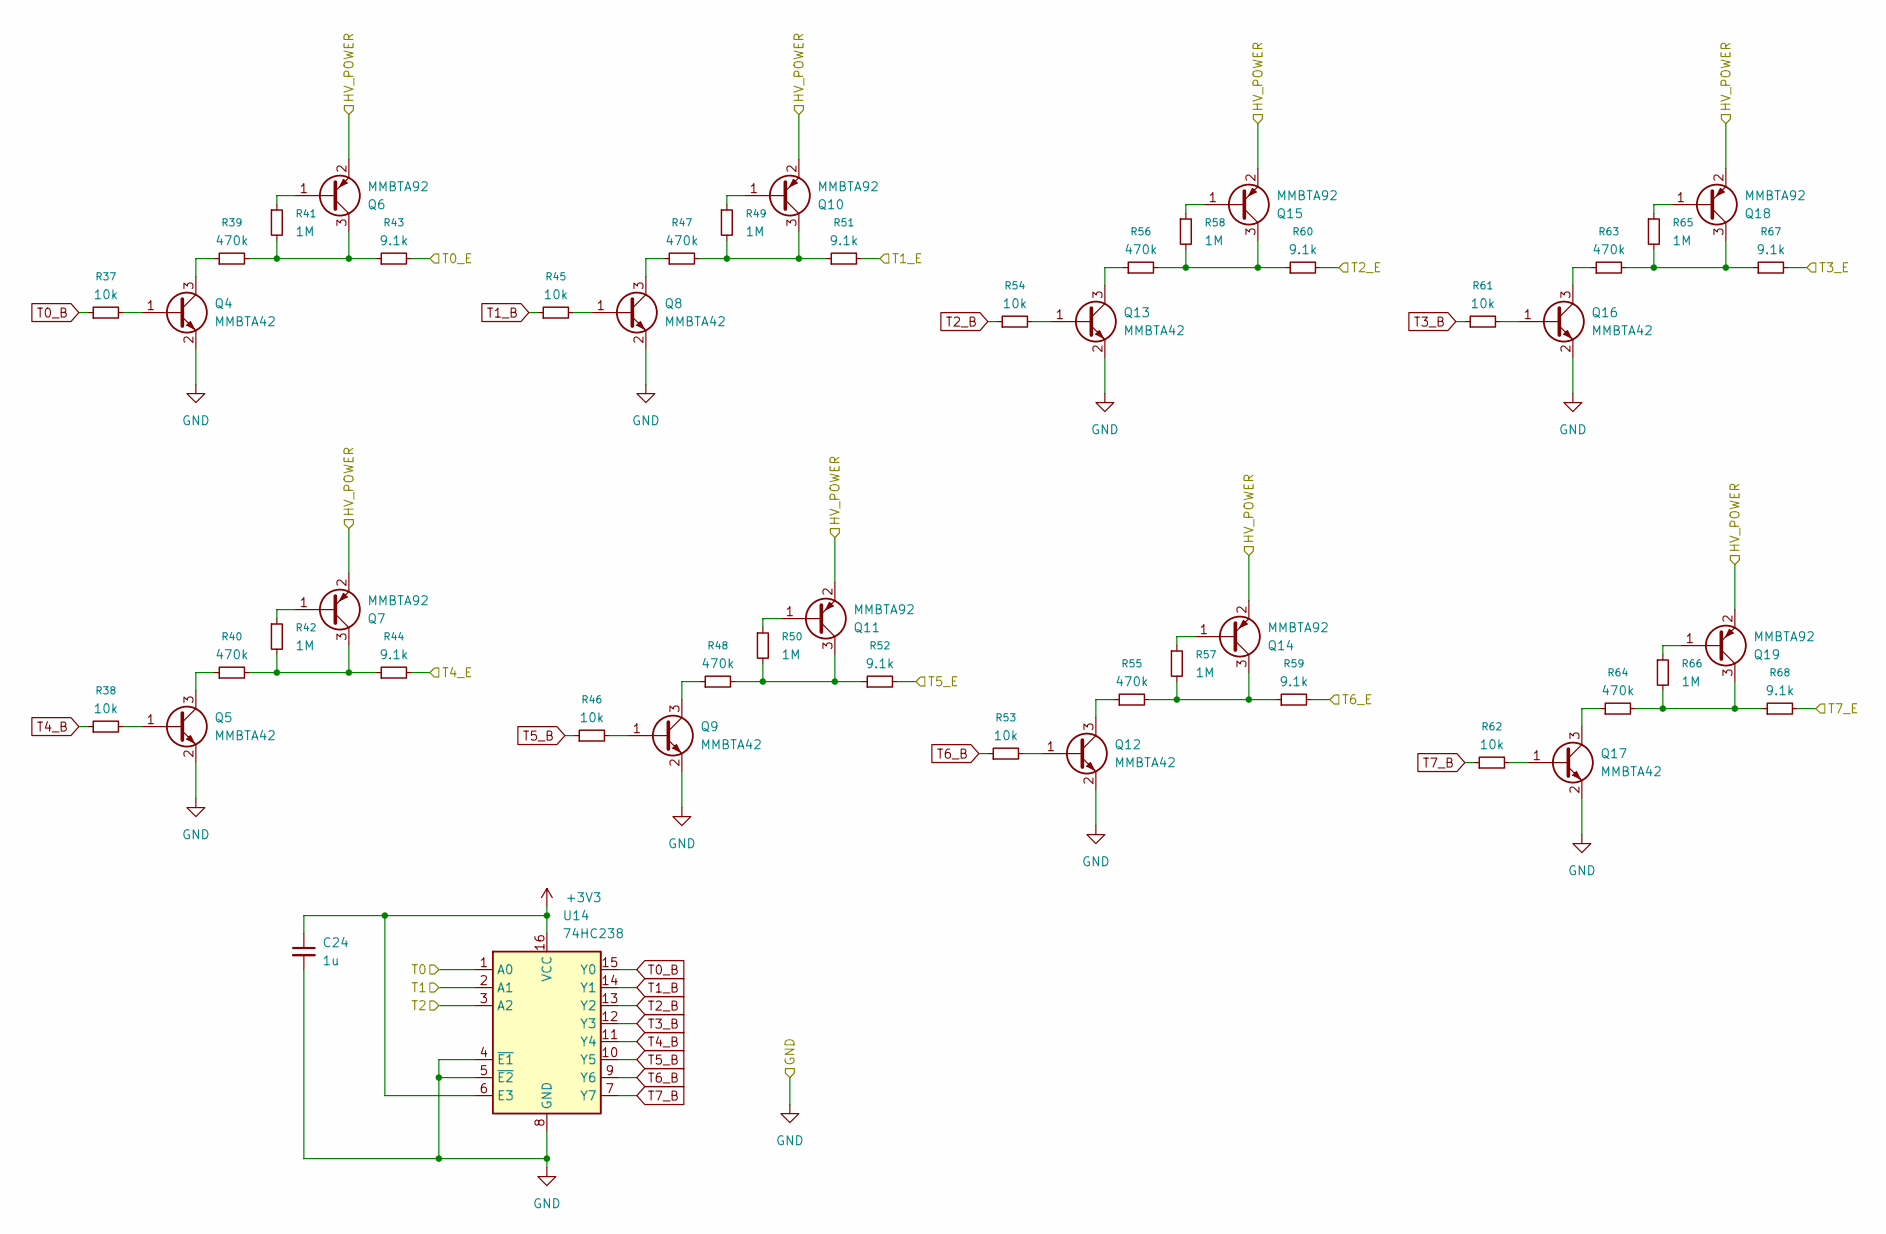
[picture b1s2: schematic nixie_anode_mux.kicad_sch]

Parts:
C24: 1u; C_0603_1608Metric; LCSC PN C5199872
Q4, Q5, Q8, Q9, Q12, Q13, Q16, Q17: MMBTA42; SOT-23; LCSC PN C94389
Q6, Q7, Q10, Q11, Q14, Q15, Q18, Q19: MMBTA92; SOT-23; LCSC PN C82049
R37, R38, R45, R46, R53, R54, R61, R62: 10k; R_0402_1005Metric; LCSC PN C25744
R39, R40, R47, R48, R55, R56, R63, R64: 470k; R_0402_1005Metric; LCSC PN C100446
R41, R42, R49, R50, R57, R58, R65, R66: 1M; R_0402_1005Metric; LCSC PN C26083
R43, R44, R51, R52, R59, R60, R67, R68: 9.1k; R_0402_1005Metric; LCSC PN C100555
U14: 74HC238; DHVQFN-16-1EP_2.5x3.5mm_P0.5mm_EP1x2mm; LCSC PN C546729

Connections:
+3V3: C24.1, U14.6 (E3), U14.16 (VCC); also elsewhere on the board
/HV_boost/PWR_HV+: Q6.2 (E), Q7.2 (E), Q10.2 (E), Q11.2 (E), Q14.2 (E), Q15.2 (E), Q18.2 (E), Q19.2 (E); also elsewhere on the board
/nixie_anode_mux/T0: U14.1 (A0); also elsewhere on the board
/nixie_anode_mux/T0_E: R43.2; also elsewhere on the board
/nixie_anode_mux/T1: U14.2 (A1); also elsewhere on the board
/nixie_anode_mux/T1_E: R51.2; also elsewhere on the board
/nixie_anode_mux/T2: U14.3 (A2); also elsewhere on the board
/nixie_anode_mux/T2_E: R60.2; also elsewhere on the board
/nixie_anode_mux/T3_E: R67.2; also elsewhere on the board
/nixie_anode_mux/T4_E: R44.2; also elsewhere on the board
/nixie_anode_mux/T5_E: R52.2; also elsewhere on the board
/nixie_anode_mux/T6_E: R59.2; also elsewhere on the board
/nixie_anode_mux/T7_E: R68.2; also elsewhere on the board
unnamed: Q4.1 (B), R37.2
unnamed: Q4.3 (C), R39.1
unnamed: Q5.1 (B), R38.2
unnamed: Q5.3 (C), R40.1
unnamed: Q6.1 (B), R41.1
unnamed: Q6.3 (C), R39.2, R41.2, R43.1
unnamed: Q7.1 (B), R42.1
unnamed: Q7.3 (C), R40.2, R42.2, R44.1
unnamed: Q8.1 (B), R45.2
unnamed: Q8.3 (C), R47.1
unnamed: Q9.1 (B), R46.2
unnamed: Q9.3 (C), R48.1
unnamed: Q10.1 (B), R49.1
unnamed: Q10.3 (C), R47.2, R49.2, R51.1
unnamed: Q11.1 (B), R50.1
unnamed: Q11.3 (C), R48.2, R50.2, R52.1
unnamed: Q12.1 (B), R53.2
unnamed: Q12.3 (C), R55.1
unnamed: Q13.1 (B), R54.2
unnamed: Q13.3 (C), R56.1
unnamed: Q14.1 (B), R57.1
unnamed: Q14.3 (C), R55.2, R57.2, R59.1
unnamed: Q15.1 (B), R58.1
unnamed: Q15.3 (C), R56.2, R58.2, R60.1
unnamed: Q16.1 (B), R61.2
unnamed: Q16.3 (C), R63.1
unnamed: Q17.1 (B), R62.2
unnamed: Q17.3 (C), R64.1
unnamed: Q18.1 (B), R65.1
unnamed: Q18.3 (C), R63.2, R65.2, R67.1
unnamed: Q19.1 (B), R66.1
unnamed: Q19.3 (C), R64.2, R66.2, R68.1
PGND1: C24.2, Q4.2 (E), Q5.2 (E), Q8.2 (E), Q9.2 (E), Q12.2 (E), Q13.2 (E), Q16.2 (E), Q17.2 (E), U14.4 (~E1), U14.5 (~E2), U14.8 (GND); also elsewhere on the board
T0_B: R37.1, U14.15 (Y0)
T1_B: R45.1, U14.14 (Y1)
T2_B: R54.1, U14.13 (Y2)
T3_B: R61.1, U14.12 (Y3)
T4_B: R38.1, U14.11 (Y4)
T5_B: R46.1, U14.10 (Y5)
T6_B: R53.1, U14.9 (Y6)
T7_B: R62.1, U14.7 (Y7)

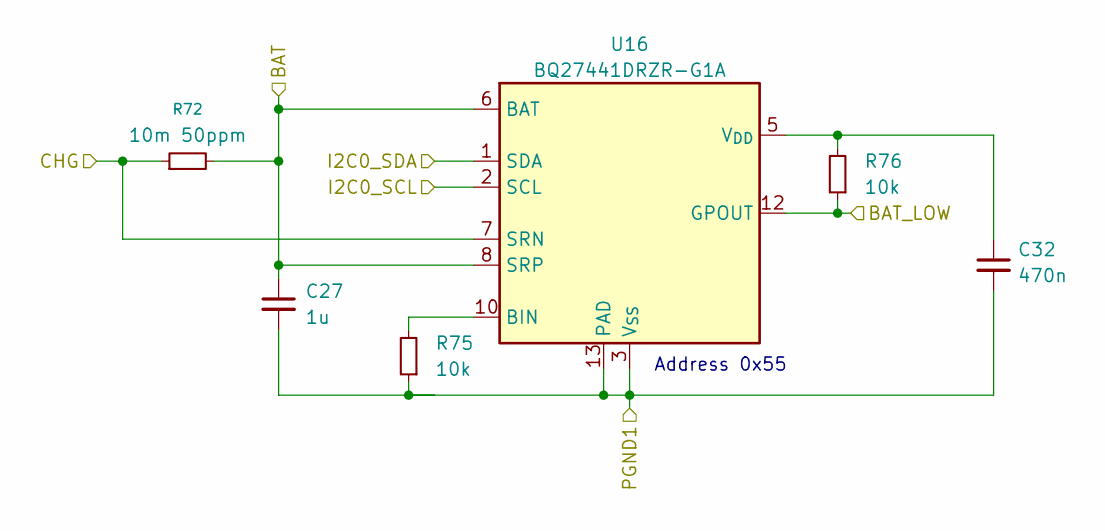
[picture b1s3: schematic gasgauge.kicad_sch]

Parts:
C27: 1u; C_0402_1005Metric
C32: 470n; C_0603_1608Metric; LCSC PN C1623
R72: 10m 50ppm; R_0805_2012Metric; LCSC PN C201254
R75, R76: 10k; R_0402_1005Metric; LCSC PN C25744
U16: BQ27441DRZR-G1A; Texas_S-PDSO-N12; LCSC PN C473397

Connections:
/Gasgauge/CHG: R72.1, U16.7 (SRN); also elsewhere on the board
BAT_LOW: R76.1, U16.12 (GPOUT); also elsewhere on the board
I2C0_SCL: U16.2 (SCL); also elsewhere on the board
I2C0_SDA: U16.1 (SDA); also elsewhere on the board
unnamed: R75.2, U16.10 (BIN)
unnamed: C32.1, R76.2, U16.5 (V_{DD})
PGND1: C27.2, C32.2, R75.1, U16.3 (V_{SS}), U16.13 (PAD); also elsewhere on the board
VBAT: C27.1, R72.2, U16.6 (BAT), U16.8 (SRP); also elsewhere on the board

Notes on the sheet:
Address 0x55

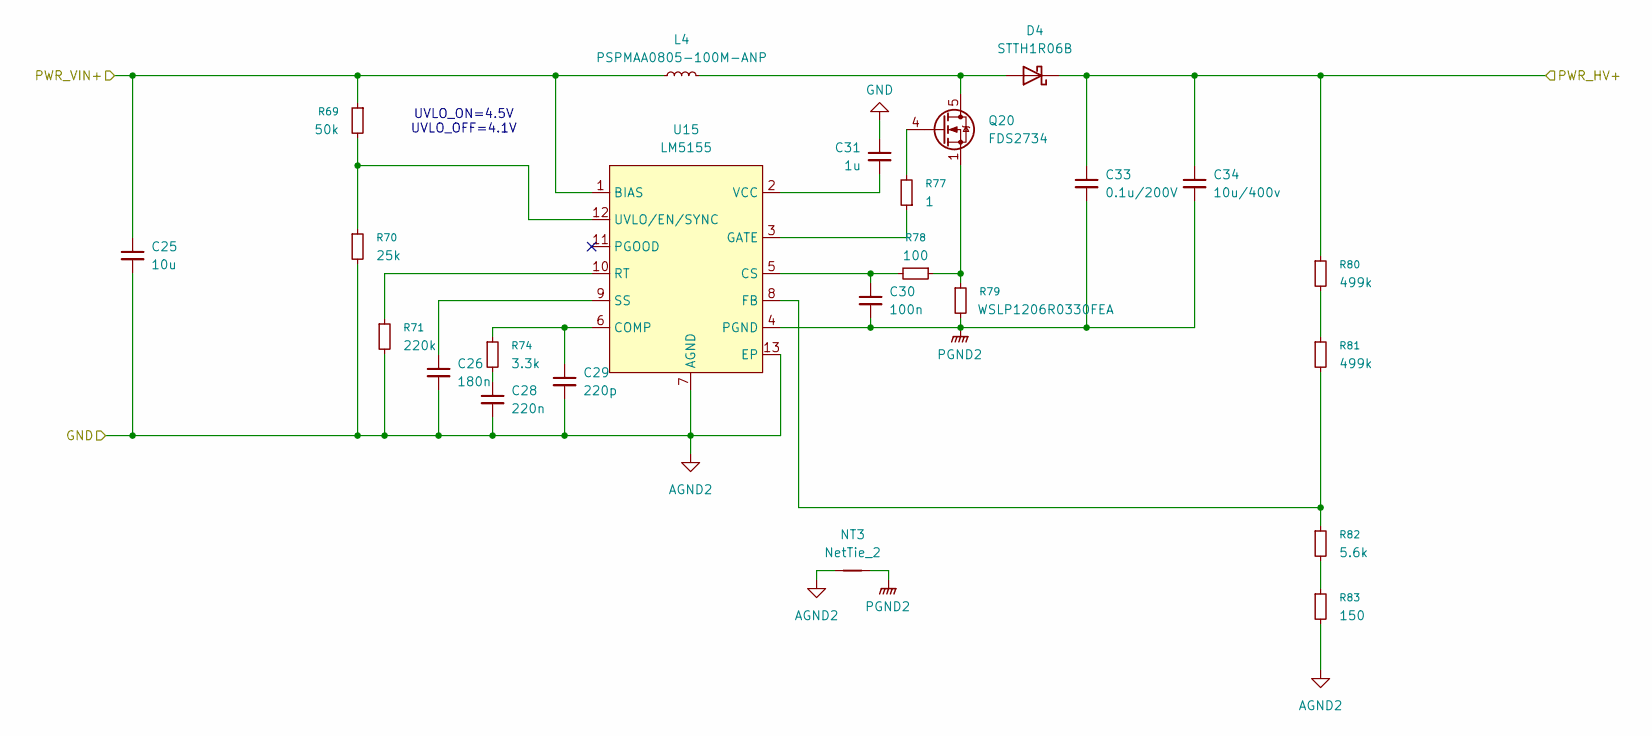
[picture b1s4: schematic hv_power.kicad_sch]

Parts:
C25: 10u; C_0805_2012Metric; LCSC PN C6119932
C26: 180n; C_0402_1005Metric; LCSC PN C309457
C28: 220n; C_0402_1005Metric; LCSC PN C16772
C29: 220p; C_0402_1005Metric; LCSC PN C1530
C30: 100n; C_0402_1005Metric; LCSC PN C1525
C31: 1u; C_0603_1608Metric; LCSC PN C5199872
C33: 0.1u/200V; C_1206_3216Metric; LCSC PN C113894
C34: 10u/400v; Cap_THT_D8.0mm_L12mm_Horizontal; LCSC PN C46867081
D4: STTH1R06B; D_SMB; LCSC PN C283526
L4: PSPMAA0805-100M-ANP; PowerInductor_8mmx8.5mm; LCSC PN C2962885
NT3: NetTie_2; NetTie-2_SMD_Pad0.5mm
Q20: FDS2734; SOIC-8_3.9x4.9mm_P1.27mm; LCSC PN C606022
R69: 50k; R_0402_1005Metric; LCSC PN C166559
R70: 25k; R_0402_1005Metric; LCSC PN C2766803
R71: 220k; R_0402_1005Metric; LCSC PN C25546
R74: 3.3k; R_0402_1005Metric; LCSC PN C25890
R77: 1; R_0402_1005Metric; LCSC PN C25086
R78: 100; R_0402_1005Metric; LCSC PN C25076
R79: WSLP1206R0330FEA; R_1206_3216Metric; LCSC PN C2084257
R80, R81: 499k; R_0402_1005Metric; LCSC PN C25793
R82: 5.6k; R_0402_1005Metric; LCSC PN C881140
R83: 150; R_0402_1005Metric; LCSC PN C25082
U15: LM5155; WSON-12-1EP_3x2mm_P0.5mm_EP1x2.65; LCSC PN C545416

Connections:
/HV_boost/PWR_HV+: C33.1, C34.1, D4.1 (K), R80.1; also elsewhere on the board
/HV_boost/PWR_VIN+: C25.1, L4.1, R69.1, U15.1 (BIAS); also elsewhere on the board
unnamed: C28.1, R74.2
unnamed: D4.2 (A), L4.2, Q20.5 (D), Q20.6 (D), Q20.7 (D), Q20.8 (D)
unnamed: Q20.4 (G), R77.2
unnamed: Q20.1 (S), Q20.2 (S), Q20.3 (S), R78.1, R79.1
unnamed: R80.2, R81.1
unnamed: R82.2, R83.1
unnamed: C29.1, R74.1, U15.6 (COMP)
unnamed: C30.1, R78.2, U15.5 (CS)
unnamed: R81.2, R82.1, U15.8 (FB)
unnamed: R77.1, U15.3 (GATE)
unnamed: R71.1, U15.10 (RT)
unnamed: C26.1, U15.9 (SS)
unnamed: R69.2, R70.1, U15.12 (UVLO/EN/SYNC)
unnamed: C31.2, U15.2 (VCC)
PGND1: C25.2, C26.2, C28.2, C29.2, C31.1, NT3.1, R70.2, R71.2, R83.2, U15.7 (AGND), U15.13 (EP); also elsewhere on the board
PGND2: C30.2, C33.2, C34.2, NT3.2, R79.2, U15.4 (PGND)

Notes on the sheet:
UVLO_ON=4.5V UVLO_OFF=4.1V

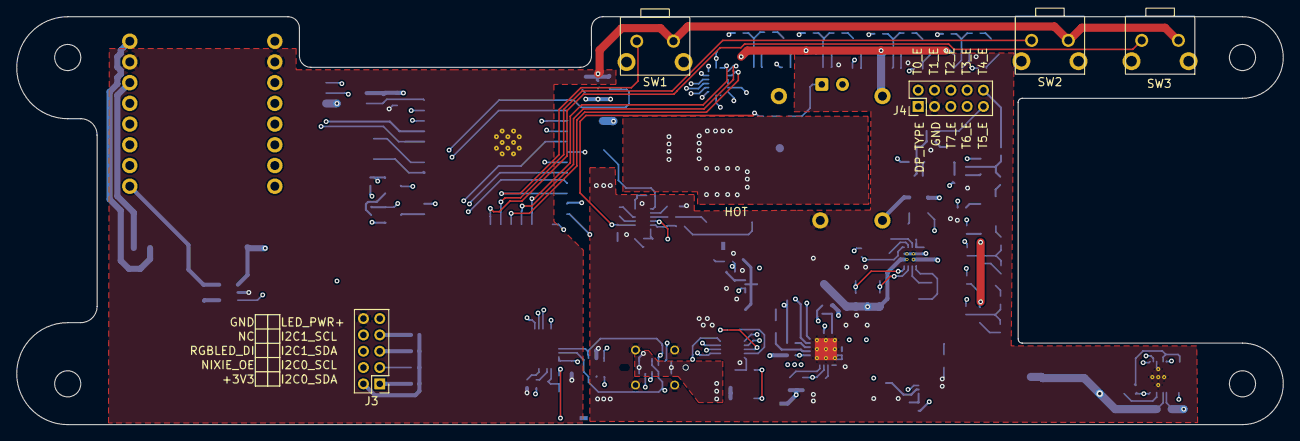
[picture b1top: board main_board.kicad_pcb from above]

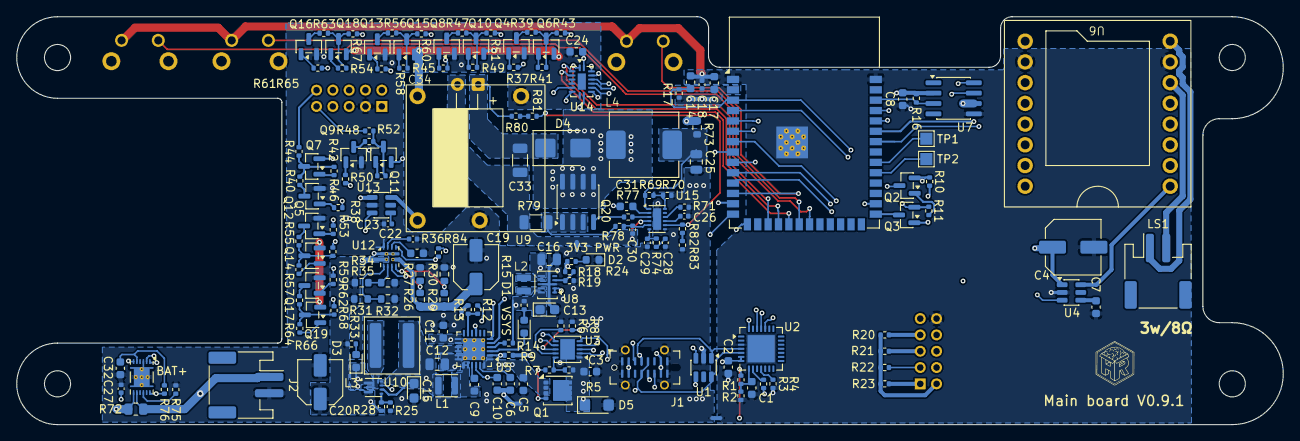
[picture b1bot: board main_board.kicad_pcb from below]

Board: 4 copper layers, 155.2 x 50.0 mm, 179 parts (170 on the bottom side), 148 nets.
